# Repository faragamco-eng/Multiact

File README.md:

# BLDC-310 — برد درایور و کنترل موتور BLDC (310 V DC، Sensorless)

> **کاربرد هدف: موتور Direct-drive کولر آبی 8000 تا 11000 (outer rotor، 1.2 kW، 450 rpm).** معماری نسخه ۲
> (PFC، FOC، شناسایی خودکار، باس دوسیمه پنل، وای‌فای) در [`docs/04_cooler_drive_architecture.md`](docs/04_cooler_drive_architecture.md) است.

درایور موتور BLDC تک‌فاز ورودی 230 VAC (باس DC حدود 310 V)، توان نامی 750 W، با **STM32G431** و
**IPM 600 V / 15 A**، به روش **Six-step sensorless (BEMF zero-crossing)**.

> ⚠️ **ولتاژ کشنده.** کل مدار، از جمله میکروکنترلر، به برق شهر متصل است. قبل از هر کاری
> [`docs/03_bringup_and_safety.md`](docs/03_bringup_and_safety.md) را بخوانید.

## محتوا

| مسیر | توضیح |
|---|---|
| [`docs/01_hardware_design.md`](docs/01_hardware_design.md) | مشخصات، بلوک دیاگرام، انتخاب قطعات، طبقه قدرت، حفاظت سه‌لایه، اندازه‌گیری، تغذیه، چیدمان |
| [`docs/02_firmware_design.md`](docs/02_firmware_design.md) | الگوریتم sensorless، ماشین حالت، استارت، نتایج شبیه‌سازی، راهنمای تیونینگ |
| [`docs/03_bringup_and_safety.md`](docs/03_bringup_and_safety.md) | راه‌اندازی سه‌مرحله‌ای، چک‌لیست PCB، عیب‌یابی |
| [`docs/04_cooler_drive_architecture.md`](docs/04_cooler_drive_architecture.md) | **کولر آبی:** تحلیل موتورها (36S/40P)، PFC، FOC، شناسایی خودکار، آلارم‌ها، نوسانات برق، باس پنل، وای‌فای |
| [`docs/05_panel_bus_modbus.md`](docs/05_panel_bus_modbus.md) | پروتکل Modbus RTU باس پنل و نقشه رجیسترها |
| [`docs/06_foc_sensorless.md`](docs/06_foc_sensorless.md) | **FOC بدون سنسور + شناسایی خودکار** (R، L، شار، اینرسی، dead-time)، حفاظت قفل روتور، نتایج 110 موتور تصادفی |
| [`docs/07_battery_solar_backup.md`](docs/07_battery_solar_backup.md) | **برق اضطراری:** ماژول باتری ۴۸ V (DAB دوطرفه) + ورودی خورشیدی روی باس DC، زمان کارکرد، نتایج شبیه‌سازی قطع برق |
| [`docs/08_firmware_v2.md`](docs/08_firmware_v2.md) | **فریمور برد v2:** ترتیب روشن شدن، اضافه‌ولتاژ 440 V، قطع برق، آلارم‌ها و تلاش مجدد، ذخیره پارامتر، بوت‌لودر و به‌روزرسانی از پنل، PHY باس پنل |
| [`docs/09_panel_and_app.md`](docs/09_panel_and_app.md) | **پنل و اپ:** تاچ یا کلید، منطق کولر (پیش‌خیس/خشک کردن)، BLE/Wi-Fi/MQTT، پیام‌های JSON، OTA، گزارش و درخواست گارانتی |
| [`hardware/v2/`](hardware/v2/) | **شماتیک و برد v2 (KiCad/Altium)**: PFC، اینورتر گسسته قابل تعمیر، باس پنل ایزوله |
| [`hardware/panel/`](hardware/panel/) | **شماتیک و برد پنل پایه (KiCad/Altium)**: ESP32-S3، نمایشگر ۴ رقمی، ۵ کلید، رابط باس دوسیمه با جریان ثابت |
| [`hardware/v2/`](hardware/v2/README.md) | **شماتیک نسخه ۲** (PFC، FOC سه‌شنت، تغذیه مقاوم 440 VAC، رله پمپ/تخلیه، باس پنل ایزوله، RS-485 ماژول باتری) — بررسی‌شده با کتابخانه KiCad و داده ST، نت‌لیست قابل import در KiCad |
| [`hardware/netlist.md`](hardware/netlist.md) | (نسخه ۱، جایگزین شده) شماتیک متنی برگه‌به‌برگه (پین‌های MCU از دیتابیس رسمی ST) |
| [`hardware/bom.csv`](hardware/bom.csv) | لیست قطعات با پارت‌نامبر نمونه |
| [`hardware/calc/`](hardware/calc/) | اسکریپت محاسبات (تلفات، هیت‌سینک، خازن، بوت‌استرپ، شنت، تقسیم‌کننده‌ها) و نتایج |
| [`firmware/`](firmware/) | فریمور C (هسته کنترل قابل حمل + BSP رجیستری) و شبیه‌ساز مدار بسته |
| [`firmware/v2/`](firmware/v2/) | فریمور برد v2: برنامه درایو، BSP، بوت‌لودر، PHY باس پنل (`make -C firmware/v2 test`) |
| [`firmware/panel/`](firmware/panel/) | فریمور پنل: هسته قابل حمل تست‌شده + اسکلت ESP32 (`make -C firmware/panel test`) |

## شروع سریع

```bash
cd firmware
make cmsis          # یک بار: دریافت هدرهای CMSIS (STM32G4)
make                # build/bldc310.elf/.bin/.hex  (arm-none-eabi-gcc)
make test           # شبیه‌سازی six-step + تست Modbus + آزمون‌های FOC روی PC (gcc)
make test-foc-random  # FOC: 40 موتور تصادفی، شناسایی از صفر و اجرا
make sweep          # مقاوم‌سازی استارت: 5 سناریو × 12 زاویه اولیه روتور
make plots          # نمودارها در docs/img (نیاز به matplotlib)
python3 hardware/calc/bldc_calc.py   # محاسبات طراحی (از ریشه مخزن)
```

فرمان‌های UART (از طریق J2 ایزوله، 115200 8N1): `run`، `stop`، `clr`، `spd <rpm>`، `dir <0|1>`، `pot <0|1>`، `?`

## وضعیت و محدودیت‌ها (صادقانه)

* ✅ فریمور برای STM32G431 بدون هشدار کامپایل می‌شود (≈ 9.8 KB فلش، 3.2 KB RAM).
* ✅ هسته کنترل در شبیه‌ساز سوئیچینگ (IPM + موتور، 0.25 µs) در هر 5 سناریو قبول می‌شود؛ استارت 59/60 در
  جاروب زاویه اولیه؛ 127/162 در جاروب ±30–40 % پارامترهای موتور ⇒ **تیونینگ برای هر موتور لازم است**.
* ⚠️ **هنوز روی سخت‌افزار واقعی تست نشده.** چند کدگذاری رجیستر که با `VERIFY` علامت خورده‌اند و پلاریته
  ورودی‌های IPM باید در راه‌اندازی مرحله ۱ تأیید شوند.
* ⚠️ بدون PFC: برای محصول تجاری، استاندارد هارمونیک (IEC 61000-3-2) و EMC باید جداگانه حل شوند.
* ⚠️ مقادیر [DS] در محاسبات (تلفات IGBT، Rth، آستانه CIN) نمونه‌اند؛ با دیتاشیت پارت نهایی جایگزین کنید.

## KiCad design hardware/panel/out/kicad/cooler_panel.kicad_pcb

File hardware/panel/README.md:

# سخت‌افزار پنل کولر — نسخه پایه (نمایشگر ۴ رقمی + کلید، Wi-Fi/BLE)

| رو (F.Cu) | پشت (B.Cu) |
|---|---|
|  |  |

## فایل‌ها

| فایل | توضیح |
|---|---|
| [`schematic.py`](schematic.py) | منبع اصلی شماتیک (هر قطعه، پین و نت) |
| [`layout.py`](layout.py) | ابعاد برد و چیدمان |
| [`out/kicad/`](out/kicad/) | **پروژه کامل KiCad 7** (۴ برگه + برد چیده‌شده). Altium: `File → Import Wizard → KiCad` |
| [`out/cooler_panel_schematic.pdf`](out/cooler_panel_schematic.pdf)، [`out/cooler_panel_placement.pdf`](out/cooler_panel_placement.pdf) | PDF |
| [`out/bom.csv`](out/bom.csv)، [`out/netlist.md`](out/netlist.md)، [`out/cooler_panel_altium_protel.net`](out/cooler_panel_altium_protel.net) | BOM، نت‌لیست خوانا، نت‌لیست Protel/Altium |
| [`out/cooler_panel_gerbers.zip`](out/cooler_panel_gerbers.zip) | **فایل‌های ساخت برد**: Gerber دولایه + دریل (Excellon) — آماده سفارش |
| [`out/cooler_panel_pick_and_place.csv`](out/cooler_panel_pick_and_place.csv) | فایل مونتاژ ماشینی (مختصات قطعات) |
| [`out/cooler_panel_routed_top.pdf`](out/cooler_panel_routed_top.pdf)، [`..._bottom.pdf`](out/cooler_panel_routed_bottom.pdf) | مسیرکشی رو و پشت |

ساخت، **مسیرکشی** و بررسی: `./build.sh` (حدود 5 تا 20 دقیقه؛ `NOROUTE=1 ./build.sh` فقط چیدمان). از ابزارها و کتابخانه‌های `hardware/v2` استفاده می‌کند.

| بررسی | نتیجه |
|---|---|
| سمبل، نام پین (از جمله **همه پین‌های ESP32-S3**)، پد footprint (کتابخانه رسمی KiCad 7.0.11) | **0 خطا، 0 هشدار** (109 قطعه، 73 نت) |
| نت‌لیستی که KiCad از شماتیک رسم‌شده خروجی گرفت در برابر طراحی | **0 اختلاف** |
| نت پدهای برد در برابر طراحی | **0 اختلاف** |
| DRC خود KiCad روی برد **مسیرکشی‌شده** | **0 خطا، 0 اتصال باز** (باقی فقط تداخل ظاهری silkscreen و اطلاعات کتابخانه) |
| ناحیه آنتن ESP32 | **بدون مس** در هر دو لایه (نه مسیر، نه via، نه پور) |

## برگه‌ها

| برگه | محتوا |
|---|---|
| ۱ رابط باس و تغذیه | ترمینال دوسیمه، فیوز PTC، TVS 33 V، پل ABS10 (بی‌تفاوت به پلاریته)، **منبع جریان ثابت LM317 (52 mA)**، خازن ذخیره 1000 µF با زنر 10 V، باک AP63203 به 3.3 V، **گیرنده** (مقایسه‌گر LMV331 روی ولتاژ باس)، **فرستنده** (سینک جریان 20 mA با BCX56)، دیود USB |
| ۲ ESP32-S3 | ماژول ESP32-S3-WROOM-1 (همان پردازنده نسخه تاچ آینده)، ریست، کلید BOOT، **USB-C** برای برنامه‌ریزی کارخانه و سرویس با محافظ ESD |
| ۳ نمایش و کلید | نمایشگر ۴ رقمی 0.56 اینچ (CC56-12SURKWA) + ۶ LED وضعیت در ۵ فاز مالتی‌پلکس، ۵ کلید، بازر، **سنسور دما و رطوبت SHT40 (آپشن، مونتاژ نمی‌شود)** |
| ۴ مکانیک | ۴ سوراخ M3، ۳ فیدوشیال، ۹ نقطه تست |

ابعاد برد: **120 × 86 mm**، دولایه 1.6 mm؛ نمایشگر، LEDها و کلیدها در جلو. آنتن ماژول رو به لبه بالا و ناحیه زیر
آنتن در هر دو لایه خالی از مس است.

## مسیرکشی

| مورد | مقدار |
|---|---|
| روش | مسیریاب دولایه پروژه (`hardware/v2/tools/autoroute.py`) با فاصله دقیق از شکل واقعی پدها، via، rip-up و مسیرکشی مجدد |
| مسیرها | 958 قطعه، مجموع 2.6 m؛ تغذیه و GND با پهنای **0.5 mm**، سیگنال‌ها 0.25 mm (8 قطعه 0.3 mm در گلوگاه‌ها) |
| via | 193 عدد، 0.6 / 0.3 mm |
| پور GND | هر دو لایه، فاصله 0.3 mm، اتصال حرارتی |
| فاصله‌ها | 0.2 mm بین مس، 0.5 mm تا لبه برد |
| نقشه پایه‌ها | پایه‌های ESP32-S3 به سمتی که مقصدشان است اختصاص داده شدند (نمایشگر راست، کلیدها پایین، باس و USB چپ) تا مسیرها از دور ماژول نگذرند |

**قبل از سفارش ساخت، در KiCad/Altium یک بار نگاه کنید:** مسیرهای ماشینی گوشه‌های زیادی دارند و جای بهینه‌سازی
ظاهری هست (Cleanup / Optimize). جفت USB D+/D− بدون کنترل امپدانس است؛ برای USB 2.0 Full-Speed در این طول کوتاه
مشکلی ندارد. سیلک‌اسکرین چند قطعه روی پد افتاده و باید جابه‌جا شود (فقط ظاهری).

## محاسبات رابط باس

| کمیت | مقدار | توضیح |
|---|---|---|
| جریان ورودی ثابت | 1.25 V / 24 Ω = **52 mA** | مستقل از مصرف لحظه‌ای وای‌فای ⇐ درایو تغییر جریان را با داده اشتباه نمی‌گیرد |
| جریان هنگام ارسال پنل | 52 + 20.4 = **73 mA** | زیر سقف 80 mA و محدودیت 150 mA درایو؛ پله 20 mA دو برابر آستانه 10 mA درایو |
| توان در دسترس | 10 V × 52 mA = 0.52 W ⇐ با بازده باک 85 %: **~134 mA در 3.3 V** | |
| مصرف تخمینی | وای‌فای متصل با modem-sleep ~45 mA + نمایشگر میانگین ~37 mA + بقیه ~5 mA = **~87 mA** | حاشیه دارد؛ اضافه در زنر تلف می‌شود (حداکثر 0.52 W، زنر 3 W) |
| پیک ارسال وای‌فای | ~350 mA در 3.3 V ⇐ کسری ~115 mA از خازن 1000 µF | 5 ms ارسال ⇐ افت 0.6 V. توان ارسال در فریمور به 15 dBm محدود شده |
| تلفات LM317 | (22.4 − 10 − 1.25) V × 52 mA = **0.58 W** | SOT-223 با مس کافی (حدود +35 K) |
| آستانه گیرنده | 2.354 V × 7.8 = **18.4 V** روی باس یکسوشده (mark 22.4 V، space 14.4 V) | پسماند 0.47 V |
| سینک فرستنده | (3.1 − 0.65) V / 120 Ω = **20.4 mA**؛ ترانزیستور 0.21 W، مقاومت 470 Ω: 0.2 W (2512) | TX در فریمور معکوس است (سینک روشن = space) |
| افت کابل | 50 m × 2 × 0.036 Ω/m × 73 mA = 0.26 V | قابل صرف‌نظر |
| شارژ اولیه | 1000 µF تا 10 V با 52 mA: **0.2 s** | |

## نقشه پایه‌های ESP32-S3 (همان `firmware/panel/esp32/main/ui_seg.c` و `bus_uart.c`)

| کاربرد | پایه |
|---|---|
| باس: TX / RX / ولتاژ (ADC) | IO17 / IO18 / IO6 |
| سگمنت a..g, dp (سمت راست ماژول، رو به نمایشگر) | IO1، IO2، IO42، IO41، IO40، IO39، IO38، IO37 |
| رقم 1..4، فاز LEDها | IO36، IO35، IO48، IO47، IO21 |
| کلیدها POWER، ▲، ▼، MODE، TIMER (پایین ماژول، رو به ردیف کلیدها) | IO10..IO14 |
| بازر / I2C سنسور | IO9 / IO4 (SDA)، IO5 (SCL) |
| USB / UART کارخانه / BOOT | IO19، IO20 / RXD0، TXD0 / IO0 |
| آزاد | IO3، IO7، IO8، IO15، IO16، IO45، IO46 |

> چون IO35–37 استفاده شده‌اند، ماژول باید **N8** (یا N8R2) باشد، نه N8R8.

## پیشنهاد جعبه و نصب

* جعبه روکار 125 × 90 mm با پنجره دودی جلوی نمایشگر و LEDها، کلیدهای ممبرین یا دکمه پلاستیکی روی کلیدهای 6 mm.
* ترمینال باس و USB در لبه پایین؛ ورود کابل از پایین (آب از بالا نفوذ نکند).
* سنسور SHT40 (اگر نصب شود) دور از رگولاتور و LM317، با شکاف در برد برای جدا کردن گرما.

## کار باقی‌مانده

مسیرکشی (دولایه، مس پهن زیر LM317 و زنر، زمین یکپارچه، بدون مس زیر آنتن)، انتخاب نهایی جعبه، و تست
روی برد: سطح سیگنال باس در طول کابل واقعی، مصرف واقعی ESP32-S3 در حالت متصل، روشنایی نمایشگر.

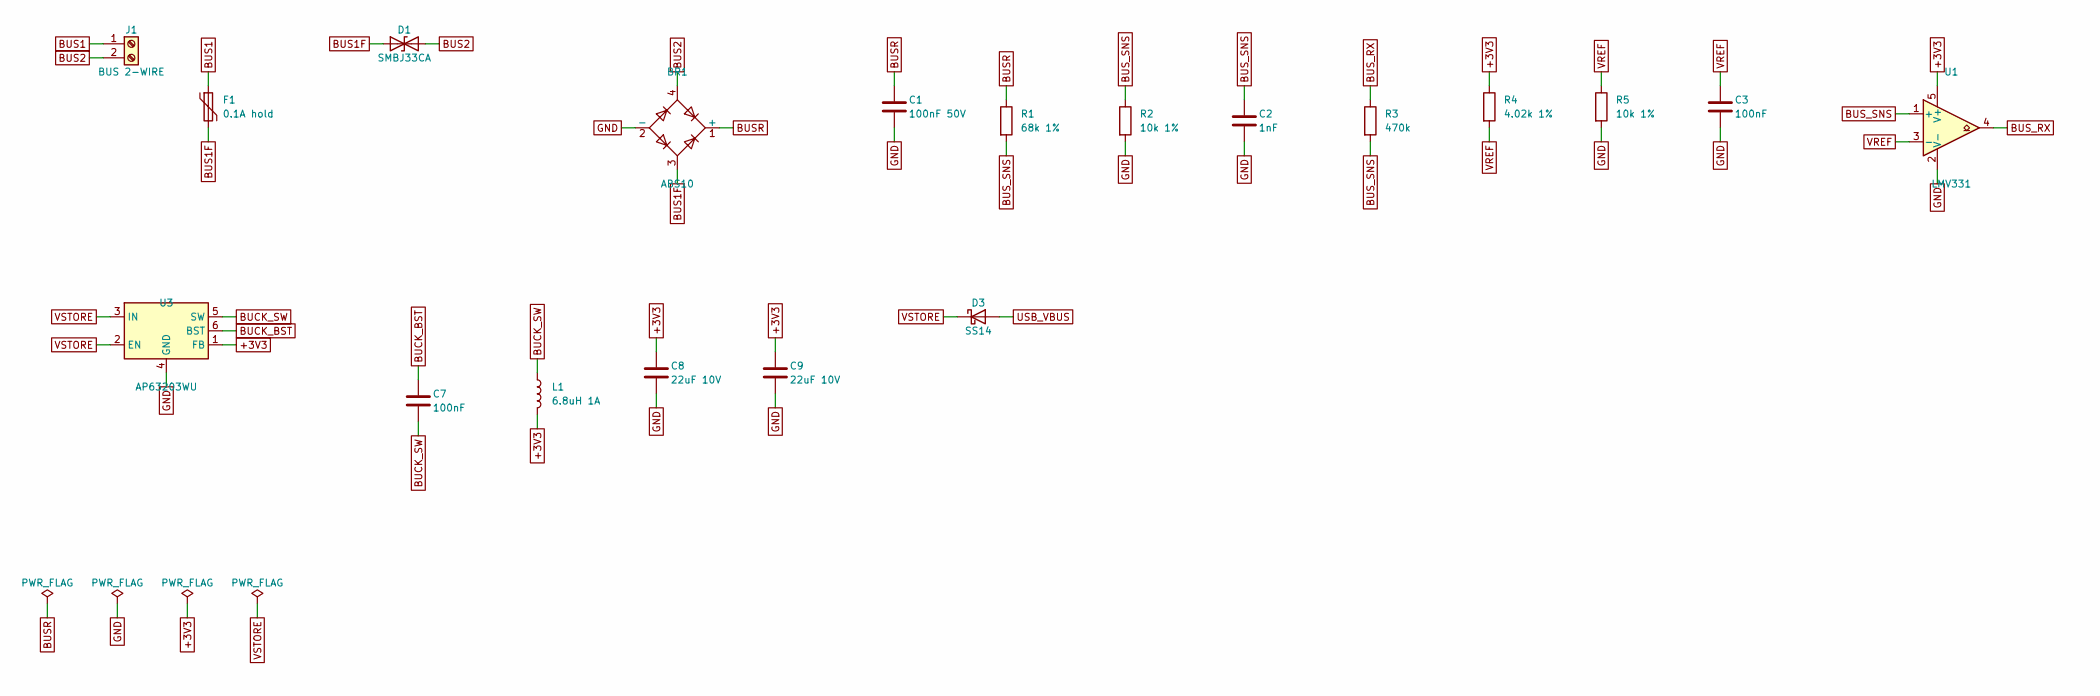
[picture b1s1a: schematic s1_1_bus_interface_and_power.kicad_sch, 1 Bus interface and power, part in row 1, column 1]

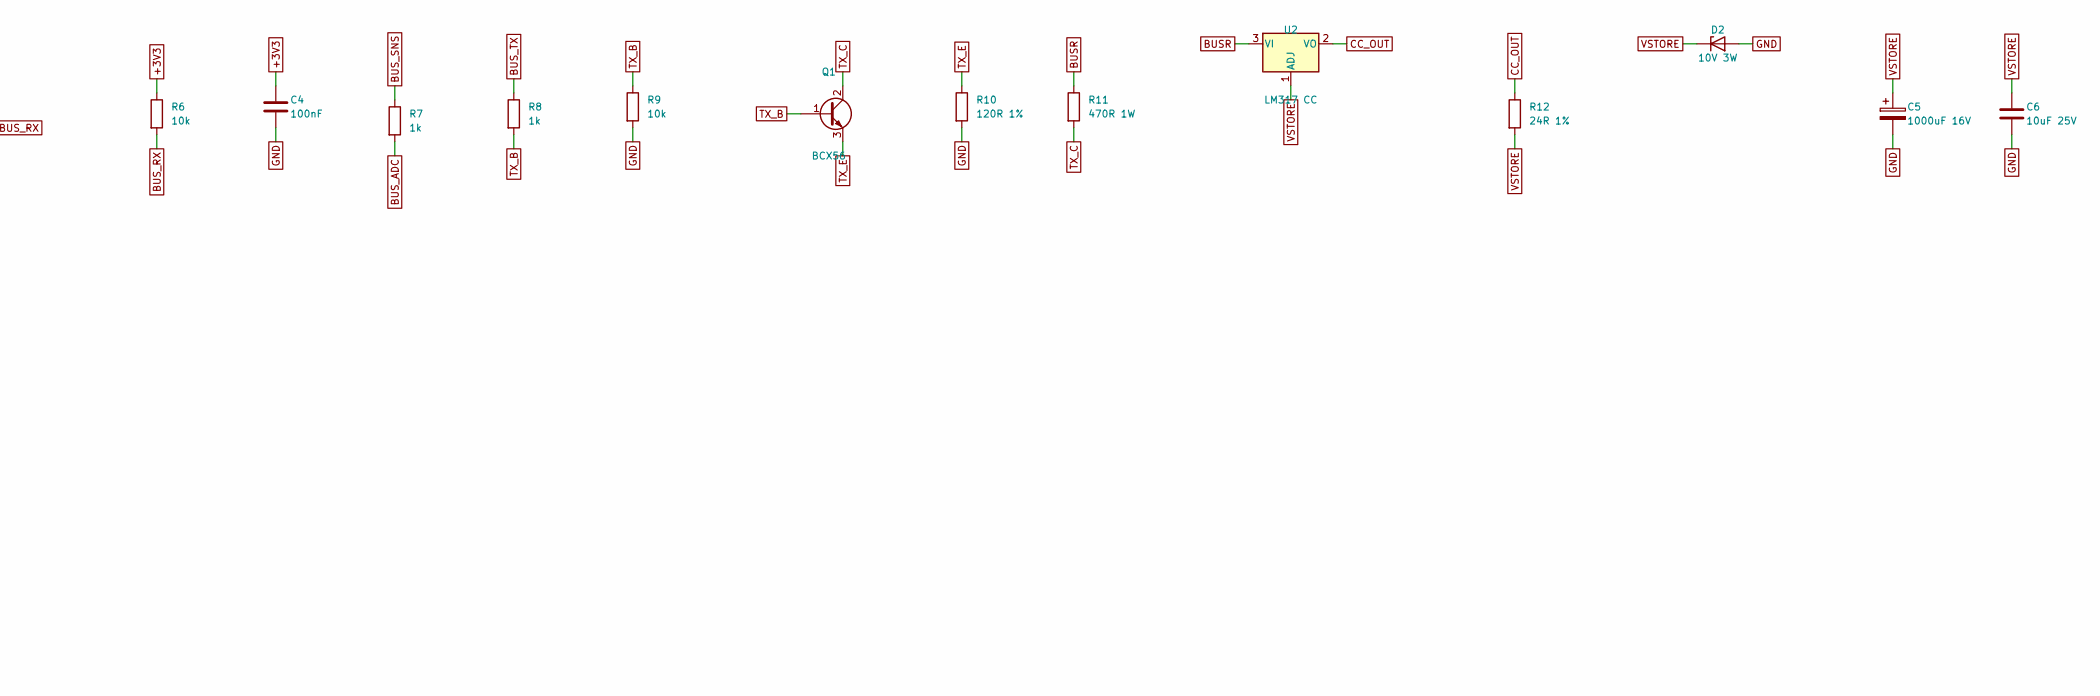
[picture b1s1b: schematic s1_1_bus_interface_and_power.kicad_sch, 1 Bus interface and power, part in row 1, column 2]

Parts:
BR1: ABS10; Diode_Bridge_Diotec_ABS; MPN Diotec ABS10 (1000 V 0.8 A)
C1: 100nF 50V; C_0805_2012Metric
C2: 1nF; C_0603_1608Metric
C3, C4, C7: 100nF; C_0603_1608Metric
C5: 1000uF 16V; CP_Radial_D10.0mm_P5.00mm; MPN low-ESR 105 C
C6: 10uF 25V; C_1206_3216Metric
C8, C9: 22uF 10V; C_1206_3216Metric
D1: SMBJ33CA; D_SMB; MPN SMBJ33CA (bidirectional)
D2: 10V 3W; D_SMB; MPN 1SMB5925BT3 (10 V 3 W)
D3: SS14; D_SMA; MPN SS14
F1: 0.1A hold; Fuse_1812_4532Metric; MPN Bourns MF-MSMF010
J1: BUS 2-WIRE; TerminalBlock_Phoenix_MKDS-1,5-2-5.08_1x02_P5.08mm_Horizont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
L1: 6.8uH 1A; L_Bourns_SRN6045TA; MPN Bourns SRN6045TA-6R8M
Q1: BCX56; SOT-89-3; MPN BCX56-16 (SOT-89, 1 W)
R1: 68k 1%; R_0603_1608Metric
R2, R5: 10k 1%; R_0603_1608Metric
R3: 470k; R_0603_1608Metric
R4: 4.02k 1%; R_0603_1608Metric
R6, R9: 10k; R_0603_1608Metric
R7, R8: 1k; R_0603_1608Metric
R10: 120R 1%; R_0603_1608Metric
R11: 470R 1W; R_2512_6332Metric
R12: 24R 1%; R_1206_3216Metric
U1: LMV331; SOT-23-5; MPN TI LMV331IDBVR (open drain)
U2: LM317 CC; SOT-223-3_TabPin2; MPN LM317DCY
U3: AP63203WU; TSOT-23-6; MPN Diodes AP63203WU (fixed 3.3 V)

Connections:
+3V3: C4.1, C8.1, C9.1, L1.2, R4.1, R6.1, U1.5 (V+), U3.1 (FB); also elsewhere on the board
BUCK_BST: C7.1, U3.6 (BST)
BUCK_SW: C7.2, L1.1, U3.5 (SW)
BUS1: F1.1, J1.1
BUS1F: BR1.3, D1.1 (A1), F1.2
BUS2: BR1.4, D1.2 (A2), J1.2
BUSR: BR1.1 (+), C1.1, R1.1, R11.1, U2.3 (VI); also elsewhere on the board
BUS_ADC: R7.2; also elsewhere on the board
BUS_RX: R3.1, R6.2, U1.4; also elsewhere on the board
BUS_SNS: C2.1, R1.2, R2.1, R3.2, R7.1, U1.1 (+)
BUS_TX: R8.1; also elsewhere on the board
CC_OUT: R12.1, U2.2 (VO)
GND: BR1.2 (-), C1.2, C2.2, C3.2, C4.2, C5.2, C6.2, C8.2, C9.2, D2.2 (A), R2.2, R5.2, R9.2, R10.2, U1.2 (V-), U3.4 (GND); also elsewhere on the board
TX_B: Q1.1 (B), R8.2, R9.1
TX_C: Q1.2 (C), R11.2
TX_E: Q1.3 (E), R10.1
USB_VBUS: D3.2 (A); also elsewhere on the board
VREF: C3.1, R4.2, R5.1, U1.3 (-)
VSTORE: C5.1, C6.1, D2.1 (K), D3.1 (K), R12.2, U2.1 (ADJ), U3.2 (EN), U3.3 (IN); also elsewhere on the board

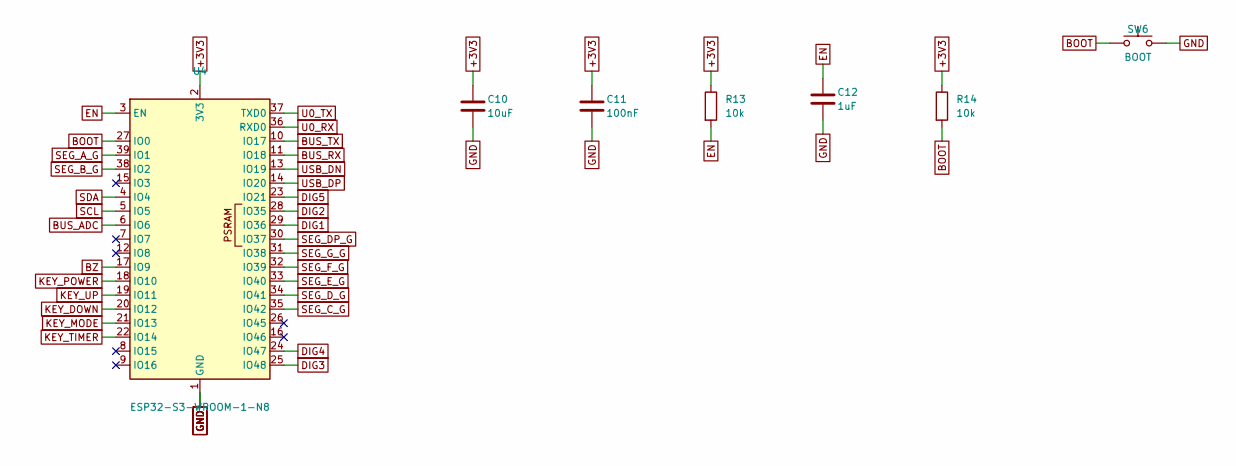
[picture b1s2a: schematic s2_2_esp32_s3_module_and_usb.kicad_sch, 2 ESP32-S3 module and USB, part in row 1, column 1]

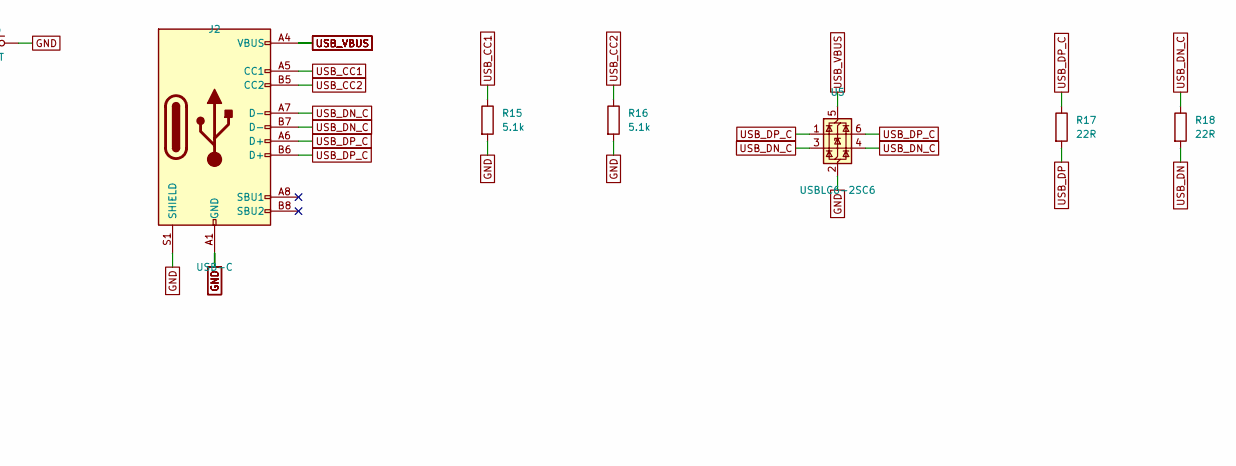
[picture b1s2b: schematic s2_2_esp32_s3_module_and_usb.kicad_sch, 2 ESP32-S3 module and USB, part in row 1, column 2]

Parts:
C10: 10uF; C_0805_2012Metric
C11: 100nF; C_0603_1608Metric
C12: 1uF; C_0603_1608Metric
J2: USB-C; USB_C_Receptacle_GCT_USB4105-xx-A_16P_TopMnt_Horizontal; MPN GCT USB4105-GF-A
R13, R14: 10k; R_0603_1608Metric
R15, R16: 5.1k; R_0603_1608Metric
R17, R18: 22R; R_0603_1608Metric
SW6: BOOT; SW_PUSH_6mm
U4: ESP32-S3-WROOM-1-N8; ESP32-S3-WROOM-1; MPN Espressif ESP32-S3-WROOM-1-N8 (NOT an R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
U5: USBLC6-2SC6; SOT-23-6; MPN ST USBLC6-2SC6

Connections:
+3V3: C10.1, C11.1, R13.1, R14.1, U4.2 (3V3); also elsewhere on the board
BOOT: R14.2, SW6.1, U4.27 (IO0)
BUS_ADC: U4.6 (IO6); also elsewhere on the board
BUS_RX: U4.11 (IO18); also elsewhere on the board
BUS_TX: U4.10 (IO17); also elsewhere on the board
BZ: U4.17 (IO9); also elsewhere on the board
DIG1: U4.29 (IO36); also elsewhere on the board
DIG2: U4.28 (IO35); also elsewhere on the board
DIG3: U4.25 (IO48); also elsewhere on the board
DIG4: U4.24 (IO47); also elsewhere on the board
DIG5: U4.23 (IO21); also elsewhere on the board
EN: C12.1, R13.2, U4.3 (EN); also elsewhere on the board
GND: C10.2, C11.2, C12.2, J2.A1 (GND), J2.A12 (GND), J2.B1 (GND), J2.B12 (GND), J2.S1 (SHIELD), R15.2, R16.2, SW6.2, U4.1 (GND), U4.40 (GND), U4.41 (GND), U5.2 (GND); also elsewhere on the board
KEY_DOWN: U4.20 (IO12); also elsewhere on the board
KEY_MODE: U4.21 (IO13); also elsewhere on the board
KEY_POWER: U4.18 (IO10); also elsewhere on the board
KEY_TIMER: U4.22 (IO14); also elsewhere on the board
KEY_UP: U4.19 (IO11); also elsewhere on the board
SCL: U4.5 (IO5); also elsewhere on the board
SDA: U4.4 (IO4); also elsewhere on the board
SEG_A_G: U4.39 (IO1); also elsewhere on the board
SEG_B_G: U4.38 (IO2); also elsewhere on the board
SEG_C_G: U4.35 (IO42); also elsewhere on the board
SEG_DP_G: U4.30 (IO37); also elsewhere on the board
SEG_D_G: U4.34 (IO41); also elsewhere on the board
SEG_E_G: U4.33 (IO40); also elsewhere on the board
SEG_F_G: U4.32 (IO39); also elsewhere on the board
SEG_G_G: U4.31 (IO38); also elsewhere on the board
U0_RX: U4.36 (RXD0); also elsewhere on the board
U0_TX: U4.37 (TXD0); also elsewhere on the board
USB_CC1: J2.A5 (CC1), R15.1
USB_CC2: J2.B5 (CC2), R16.1
USB_DN: R18.2, U4.13 (IO19)
USB_DN_C: J2.A7 (D-), J2.B7 (D-), R18.1, U5.3 (I/O2), U5.4 (I/O2)
USB_DP: R17.2, U4.14 (IO20)
USB_DP_C: J2.A6 (D+), J2.B6 (D+), R17.1, U5.1 (I/O1), U5.6 (I/O1)
USB_VBUS: J2.A4 (VBUS), J2.A9 (VBUS), J2.B4 (VBUS), J2.B9 (VBUS), U5.5 (VBUS); also elsewhere on the board

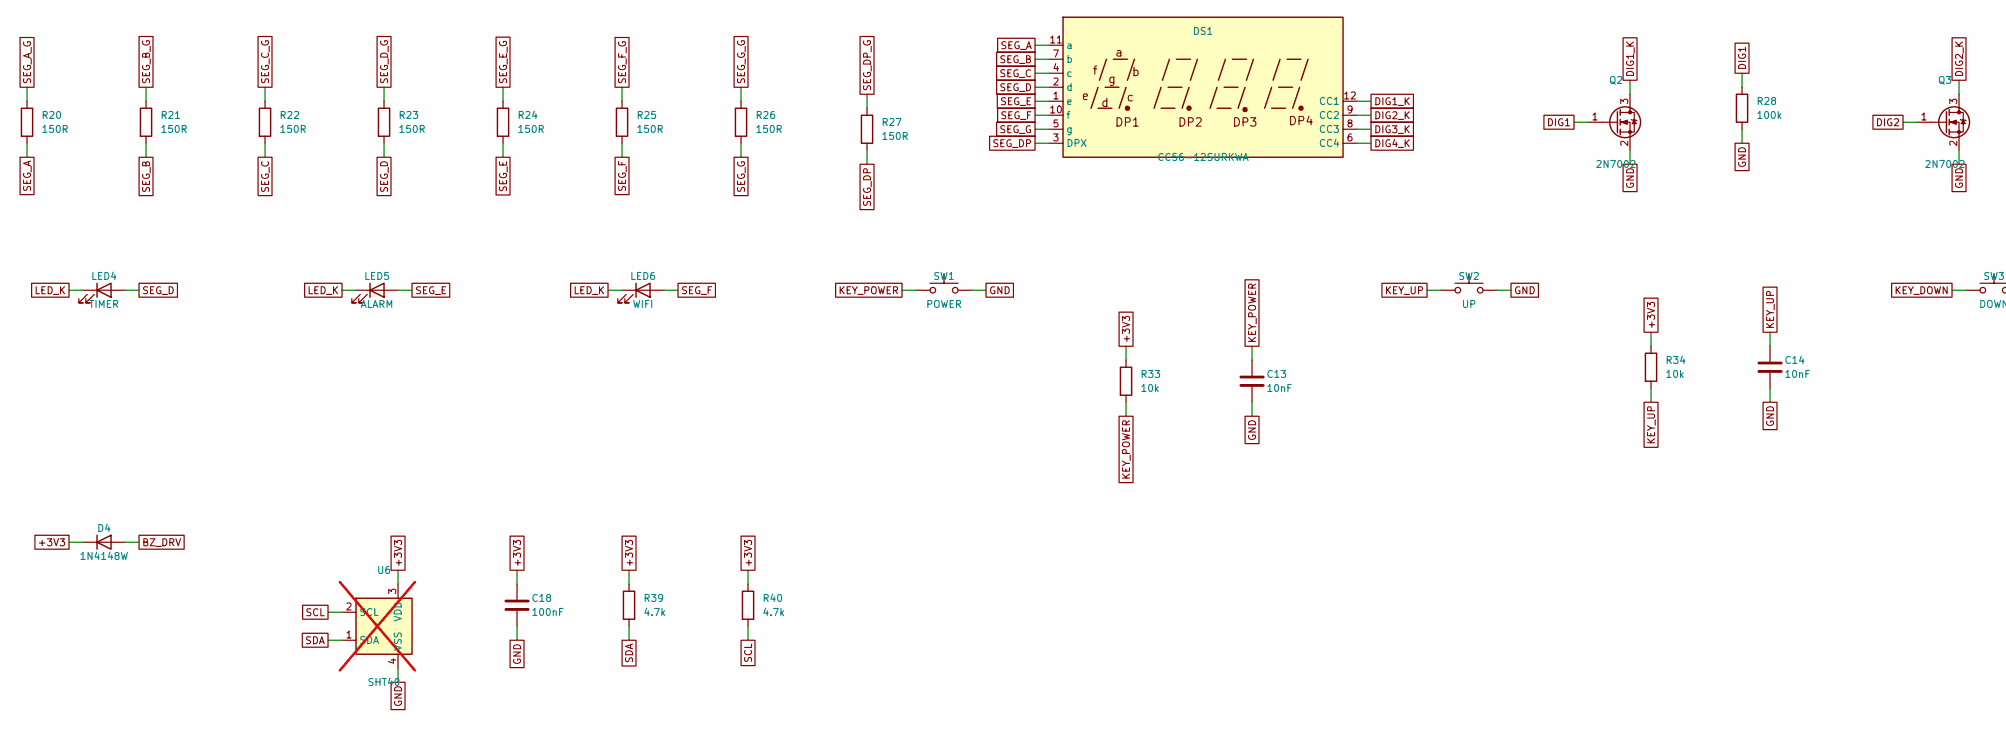
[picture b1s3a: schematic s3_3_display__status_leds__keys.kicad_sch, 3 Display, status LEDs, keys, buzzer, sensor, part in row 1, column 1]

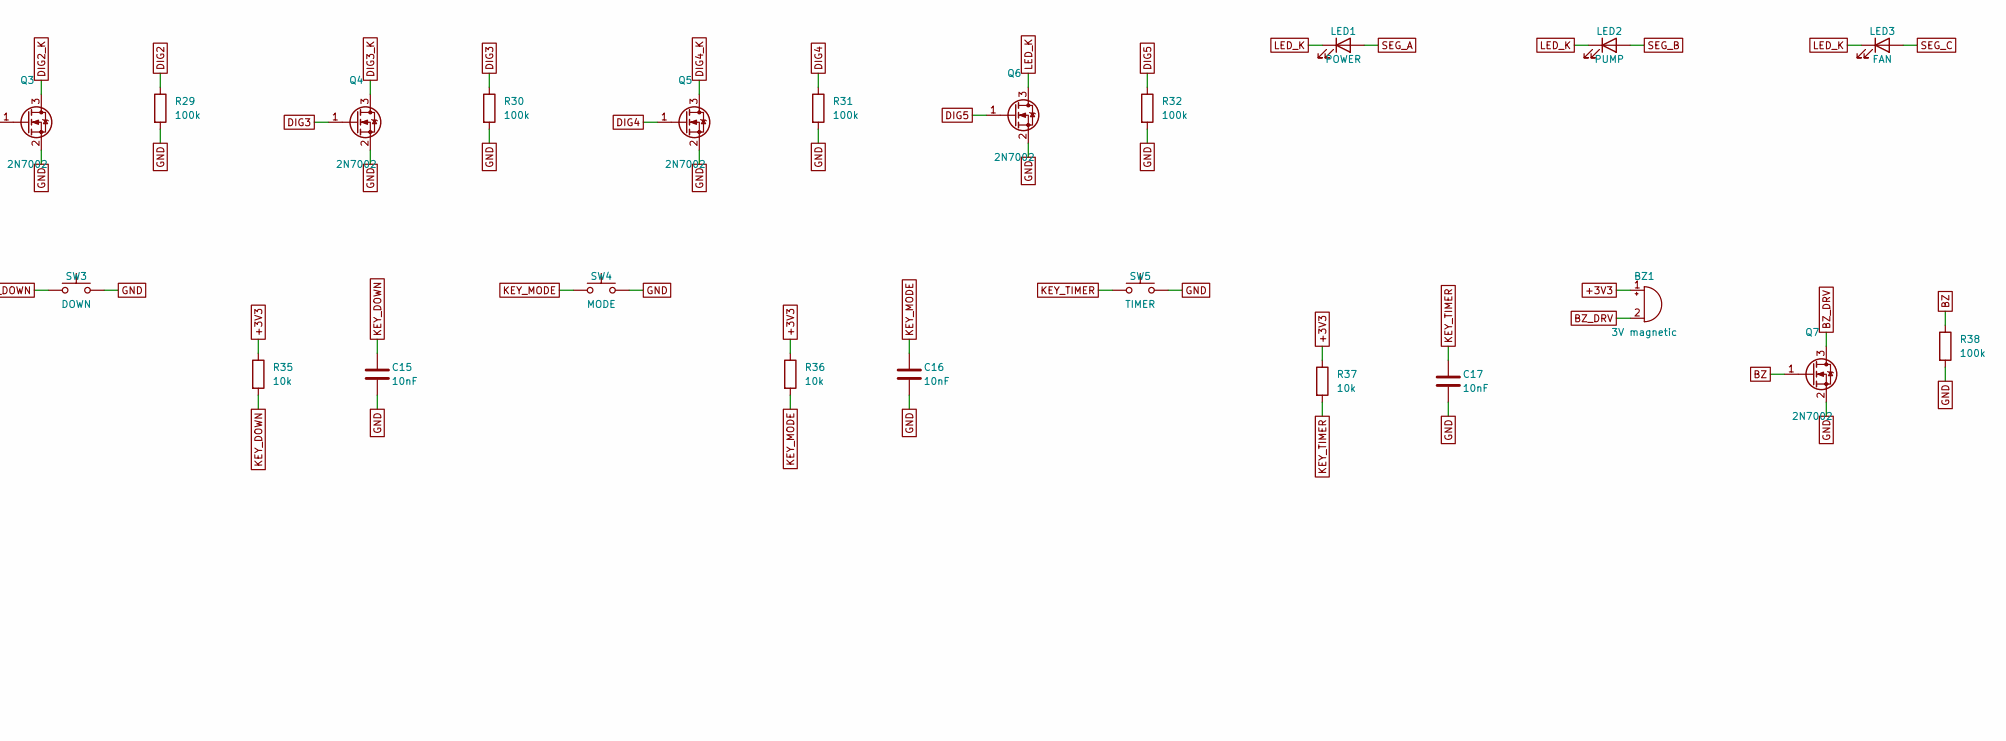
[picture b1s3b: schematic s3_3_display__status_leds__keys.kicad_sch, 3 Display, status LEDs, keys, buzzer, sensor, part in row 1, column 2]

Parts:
BZ1: 3V magnetic; Buzzer_12x9.5RM7.6; MPN magnetic buzzer 3 V, 2.7 kHz (e.g. CUI 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
C13, C14, C15, C16, C17: 10nF; C_0603_1608Metric
C18: 100nF; C_0603_1608Metric
D4: 1N4148W; D_SOD-123; MPN 1N4148W
DS1: CC56-12SURKWA; CA56-12EWA; MPN Kingbright CC56-12SURKWA (0.56 in, supe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
LED1: POWER; LED_0805_2012Metric; MPN green
LED2: PUMP; LED_0805_2012Metric; MPN green
LED3: FAN; LED_0805_2012Metric; MPN green
LED4: TIMER; LED_0805_2012Metric; MPN green
LED5: ALARM; LED_0805_2012Metric; MPN red
LED6: WIFI; LED_0805_2012Metric; MPN blue
Q2, Q3, Q4, Q5, Q6, Q7: 2N7002; SOT-23; MPN 2N7002
R20, R21, R22, R23, R24, R25, R26, R27: 150R; R_0603_1608Metric
R28, R29, R30, R31, R32, R38: 100k; R_0603_1608Metric
R33, R34, R35, R36, R37: 10k; R_0603_1608Metric
R39, R40: 4.7k; R_0603_1608Metric
SW1: POWER; SW_PUSH_6mm
SW2: UP; SW_PUSH_6mm
SW3: DOWN; SW_PUSH_6mm
SW4: MODE; SW_PUSH_6mm
SW5: TIMER; SW_PUSH_6mm
U6: SHT40; Sensirion_DFN-4_1.5x1.5mm_P0.8mm_SHT4x_NoCentralPad; MPN Sensirion SHT40-AD1B; not fitted

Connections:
+3V3: BZ1.1 (+), C18.1, D4.1 (K), R33.1, R34.1, R35.1, R36.1, R37.1, R39.1, R40.1, U6.3 (VDD); also elsewhere on the board
BZ: Q7.1 (G), R38.1; also elsewhere on the board
BZ_DRV: BZ1.2 (-), D4.2 (A), Q7.3 (D)
DIG1: Q2.1 (G), R28.1; also elsewhere on the board
DIG1_K: DS1.12 (CC1), Q2.3 (D)
DIG2: Q3.1 (G), R29.1; also elsewhere on the board
DIG2_K: DS1.9 (CC2), Q3.3 (D)
DIG3: Q4.1 (G), R30.1; also elsewhere on the board
DIG3_K: DS1.8 (CC3), Q4.3 (D)
DIG4: Q5.1 (G), R31.1; also elsewhere on the board
DIG4_K: DS1.6 (CC4), Q5.3 (D)
DIG5: Q6.1 (G), R32.1; also elsewhere on the board
GND: C13.2, C14.2, C15.2, C16.2, C17.2, C18.2, Q2.2 (S), Q3.2 (S), Q4.2 (S), Q5.2 (S), Q6.2 (S), Q7.2 (S), R28.2, R29.2, R30.2, R31.2, R32.2, R38.2, SW1.2, SW2.2, SW3.2, SW4.2, SW5.2, U6.4 (VSS); also elsewhere on the board
KEY_DOWN: C15.1, R35.2, SW3.1; also elsewhere on the board
KEY_MODE: C16.1, R36.2, SW4.1; also elsewhere on the board
KEY_POWER: C13.1, R33.2, SW1.1; also elsewhere on the board
KEY_TIMER: C17.1, R37.2, SW5.1; also elsewhere on the board
KEY_UP: C14.1, R34.2, SW2.1; also elsewhere on the board
LED_K: LED1.1 (K), LED2.1 (K), LED3.1 (K), LED4.1 (K), LED5.1 (K), LED6.1 (K), Q6.3 (D)
SCL: R40.2, U6.2 (SCL); also elsewhere on the board
SDA: R39.2, U6.1 (SDA); also elsewhere on the board
SEG_A: DS1.11 (a), LED1.2 (A), R20.2
SEG_A_G: R20.1; also elsewhere on the board
SEG_B: DS1.7 (b), LED2.2 (A), R21.2
SEG_B_G: R21.1; also elsewhere on the board
SEG_C: DS1.4 (c), LED3.2 (A), R22.2
SEG_C_G: R22.1; also elsewhere on the board
SEG_D: DS1.2 (d), LED4.2 (A), R23.2
SEG_DP: DS1.3 (DPX), R27.2
SEG_DP_G: R27.1; also elsewhere on the board
SEG_D_G: R23.1; also elsewhere on the board
SEG_E: DS1.1 (e), LED5.2 (A), R24.2
SEG_E_G: R24.1; also elsewhere on the board
SEG_F: DS1.10 (f), LED6.2 (A), R25.2
SEG_F_G: R25.1; also elsewhere on the board
SEG_G: DS1.5 (g), R26.2
SEG_G_G: R26.1; also elsewhere on the board

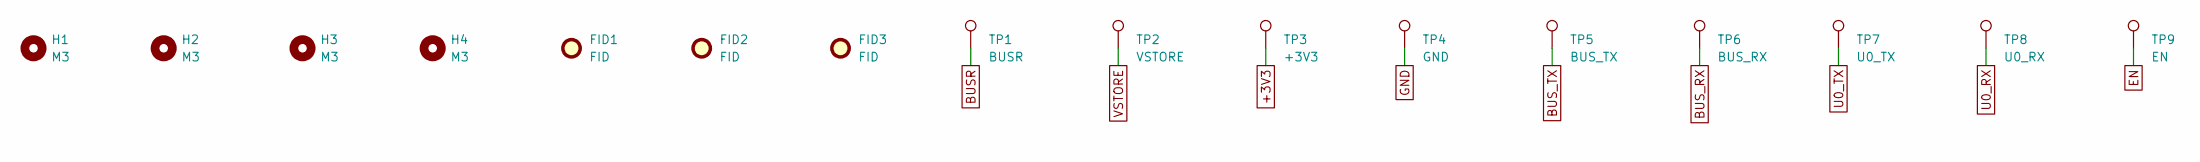
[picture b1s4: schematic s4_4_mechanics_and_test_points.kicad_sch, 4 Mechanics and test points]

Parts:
FID1, FID2, FID3: FID; Fiducial_1mm_Mask2mm
H1, H2, H3, H4: M3; MountingHole_3.2mm_M3
TP1: BUSR; TestPoint_Pad_D1.5mm
TP2: VSTORE; TestPoint_Pad_D1.5mm
TP3: +3V3; TestPoint_Pad_D1.5mm
TP4: GND; TestPoint_Pad_D1.5mm
TP5: BUS_TX; TestPoint_Pad_D1.5mm
TP6: BUS_RX; TestPoint_Pad_D1.5mm
TP7: U0_TX; TestPoint_Pad_D1.5mm
TP8: U0_RX; TestPoint_Pad_D1.5mm
TP9: EN; TestPoint_Pad_D1.5mm

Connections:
+3V3: TP3.1; also elsewhere on the board
BUSR: TP1.1; also elsewhere on the board
BUS_RX: TP6.1; also elsewhere on the board
BUS_TX: TP5.1; also elsewhere on the board
EN: TP9.1; also elsewhere on the board
GND: TP4.1; also elsewhere on the board
U0_RX: TP8.1; also elsewhere on the board
U0_TX: TP7.1; also elsewhere on the board
VSTORE: TP2.1; also elsewhere on the board

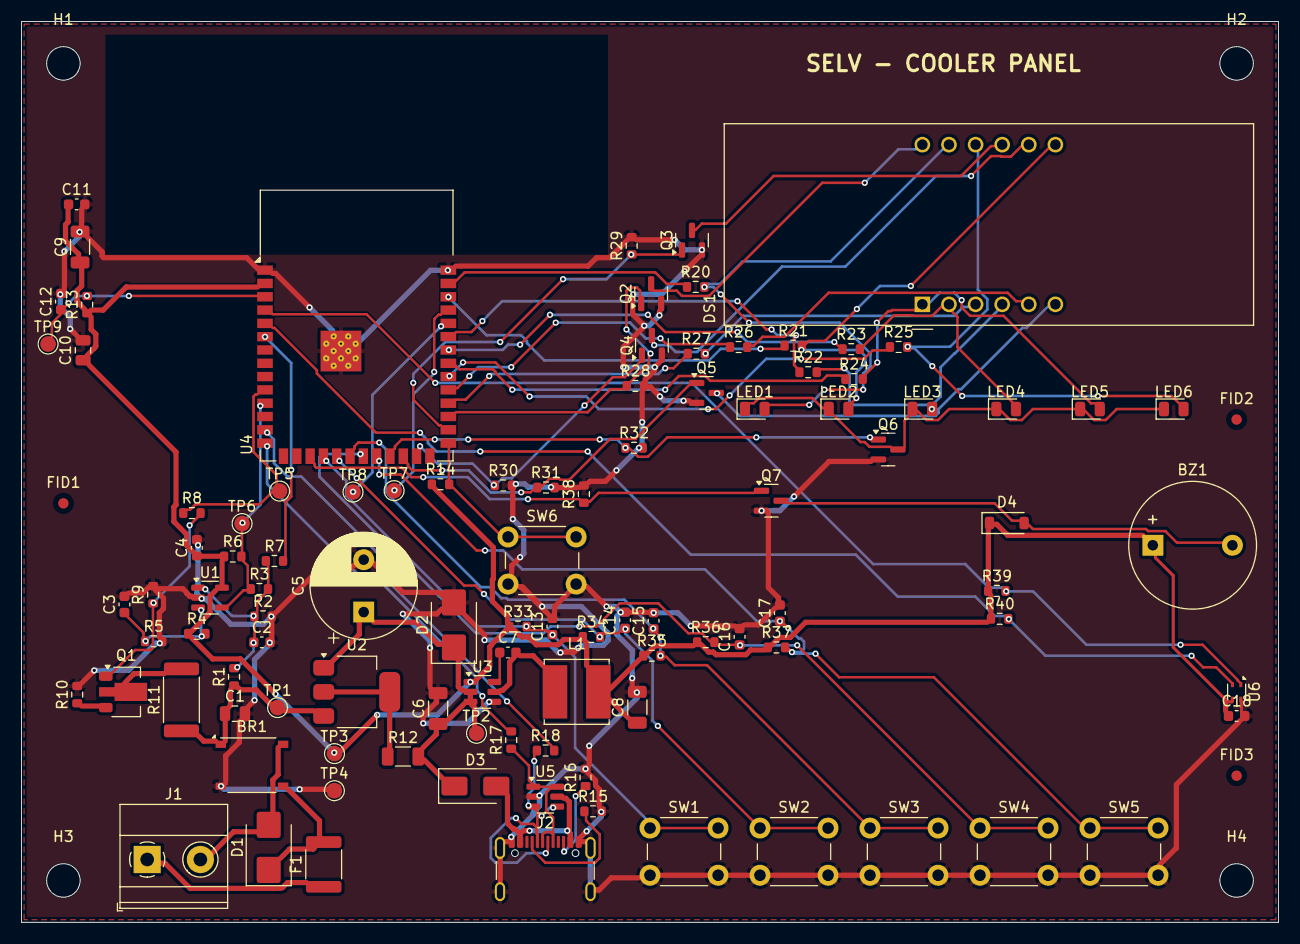
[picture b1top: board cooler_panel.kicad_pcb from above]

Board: 2 copper layers, 120.0 x 86.0 mm, 109 parts (0 on the bottom side), 64 nets.

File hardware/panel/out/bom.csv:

Qty,References,Value,MPN / description,Footprint,Populate
1,J1,BUS 2-WIRE,,"TerminalBlock_Phoenix:TerminalBlock_Phoenix_MKDS-1,5-2-5.08_1x02_P5.08mm_Horizontal",yes
1,F1,0.1A hold,Bourns MF-MSMF010,Fuse:Fuse_1812_4532Metric,yes
1,D1,SMBJ33CA,SMBJ33CA (bidirectional),Diode_SMD:D_SMB,yes
1,BR1,ABS10,Diotec ABS10 (1000 V 0.8 A),Diode_SMD:Diode_Bridge_Diotec_ABS,yes
1,C1,100nF 50V,,Capacitor_SMD:C_0805_2012Metric,yes
1,R1,68k 1%,,Resistor_SMD:R_0603_1608Metric,yes
2,R2 R5,10k 1%,,Resistor_SMD:R_0603_1608Metric,yes
1,C2,1nF,,Capacitor_SMD:C_0603_1608Metric,yes
1,R3,470k,,Resistor_SMD:R_0603_1608Metric,yes
1,R4,4.02k 1%,,Resistor_SMD:R_0603_1608Metric,yes
5,C3 C4 C7 C11 C18,100nF,,Capacitor_SMD:C_0603_1608Metric,yes
1,U1,LMV331,TI LMV331IDBVR (open drain),Package_TO_SOT_SMD:SOT-23-5,yes
9,R6 R9 R13 R14 R33 R34 R35 R36 R37,10k,,Resistor_SMD:R_0603_1608Metric,yes
2,R7 R8,1k,,Resistor_SMD:R_0603_1608Metric,yes
1,Q1,BCX56,"BCX56-16 (SOT-89, 1 W)",Package_TO_SOT_SMD:SOT-89-3,yes
1,R10,120R 1%,,Resistor_SMD:R_0603_1608Metric,yes
1,R11,470R 1W,,Resistor_SMD:R_2512_6332Metric,yes
1,U2,LM317 CC,LM317DCY,Package_TO_SOT_SMD:SOT-223-3_TabPin2,yes
1,R12,24R 1%,,Resistor_SMD:R_1206_3216Metric,yes
1,D2,10V 3W,1SMB5925BT3 (10 V 3 W),Diode_SMD:D_SMB,yes
1,C5,1000uF 16V,low-ESR 105 C,Capacitor_THT:CP_Radial_D10.0mm_P5.00mm,yes
1,C6,10uF 25V,,Capacitor_SMD:C_1206_3216Metric,yes
1,U3,AP63203WU,Diodes AP63203WU (fixed 3.3 V),Package_TO_SOT_SMD:TSOT-23-6,yes
1,L1,6.8uH 1A,Bourns SRN6045TA-6R8M,Inductor_SMD:L_Bourns_SRN6045TA,yes
2,C8 C9,22uF 10V,,Capacitor_SMD:C_1206_3216Metric,yes
1,D3,SS14,SS14,Diode_SMD:D_SMA,yes
1,U4,ESP32-S3-WROOM-1-N8,Espressif ESP32-S3-WROOM-1-N8 (NOT an R8 variant: IO35-37 are used),RF_Module:ESP32-S3-WROOM-1,yes
1,C10,10uF,,Capacitor_SMD:C_0805_2012Metric,yes
1,C12,1uF,,Capacitor_SMD:C_0603_1608Metric,yes
1,SW6,BOOT,,Button_Switch_THT:SW_PUSH_6mm,yes
1,J2,USB-C,GCT USB4105-GF-A,Connector_USB:USB_C_Receptacle_GCT_USB4105-xx-A_16P_TopMnt_Horizontal,yes
2,R15 R16,5.1k,,Resistor_SMD:R_0603_1608Metric,yes
1,U5,USBLC6-2SC6,ST USBLC6-2SC6,Package_TO_SOT_SMD:SOT-23-6,yes
2,R17 R18,22R,,Resistor_SMD:R_0603_1608Metric,yes
8,R20 R21 R22 R23 R24 R25 R26 R27,150R,,Resistor_SMD:R_0603_1608Metric,yes
1,DS1,CC56-12SURKWA,"Kingbright CC56-12SURKWA (0.56 in, super-bright red, common cathode)",Display_7Segment:CA56-12EWA,yes
6,Q2 Q3 Q4 Q5 Q6 Q7,2N7002,2N7002,Package_TO_SOT_SMD:SOT-23,yes
6,R28 R29 R30 R31 R32 R38,100k,,Resistor_SMD:R_0603_1608Metric,yes
1,LED1,POWER,green,LED_SMD:LED_0805_2012Metric,yes
1,LED2,PUMP,green,LED_SMD:LED_0805_2012Metric,yes
1,LED3,FAN,green,LED_SMD:LED_0805_2012Metric,yes
1,LED4,TIMER,green,LED_SMD:LED_0805_2012Metric,yes
1,LED5,ALARM,red,LED_SMD:LED_0805_2012Metric,yes
1,LED6,WIFI,blue,LED_SMD:LED_0805_2012Metric,yes
1,SW1,POWER,,Button_Switch_THT:SW_PUSH_6mm,yes
5,C13 C14 C15 C16 C17,10nF,,Capacitor_SMD:C_0603_1608Metric,yes
1,SW2,UP,,Button_Switch_THT:SW_PUSH_6mm,yes
1,SW3,DOWN,,Button_Switch_THT:SW_PUSH_6mm,yes
1,SW4,MODE,,Button_Switch_THT:SW_PUSH_6mm,yes
1,SW5,TIMER,,Button_Switch_THT:SW_PUSH_6mm,yes
1,BZ1,3V magnetic,"magnetic buzzer 3 V, 2.7 kHz (e.g. CUI CMT-1203)",Buzzer_Beeper:Buzzer_12x9.5RM7.6,yes
1,D4,1N4148W,1N4148W,Diode_SMD:D_SOD-123,yes
1,U6,SHT40,Sensirion SHT40-AD1B,Sensor_Humidity:Sensirion_DFN-4_1.5x1.5mm_P0.8mm_SHT4x_NoCentralPad,OPTION/DNP
2,R39 R40,4.7k,,Resistor_SMD:R_0603_1608Metric,yes
4,H1 H2 H3 H4,M3,,MountingHole:MountingHole_3.2mm_M3,yes
3,FID1 FID2 FID3,FID,,Fiducial:Fiducial_1mm_Mask2mm,yes
1,TP1,BUSR,,TestPoint:TestPoint_Pad_D1.5mm,yes
1,TP2,VSTORE,,TestPoint:TestPoint_Pad_D1.5mm,yes
1,TP3,+3V3,,TestPoint:TestPoint_Pad_D1.5mm,yes
1,TP4,GND,,TestPoint:TestPoint_Pad_D1.5mm,yes
1,TP5,BUS_TX,,TestPoint:TestPoint_Pad_D1.5mm,yes
1,TP6,BUS_RX,,TestPoint:TestPoint_Pad_D1.5mm,yes
1,TP7,U0_TX,,TestPoint:TestPoint_Pad_D1.5mm,yes
1,TP8,U0_RX,,TestPoint:TestPoint_Pad_D1.5mm,yes
1,TP9,EN,,TestPoint:TestPoint_Pad_D1.5mm,yes
